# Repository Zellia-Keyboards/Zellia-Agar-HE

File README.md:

# Zellia-Agar-HE
## Use with Kicad 8.0.9
## Sensor just place SLSS49E for replace part in order later

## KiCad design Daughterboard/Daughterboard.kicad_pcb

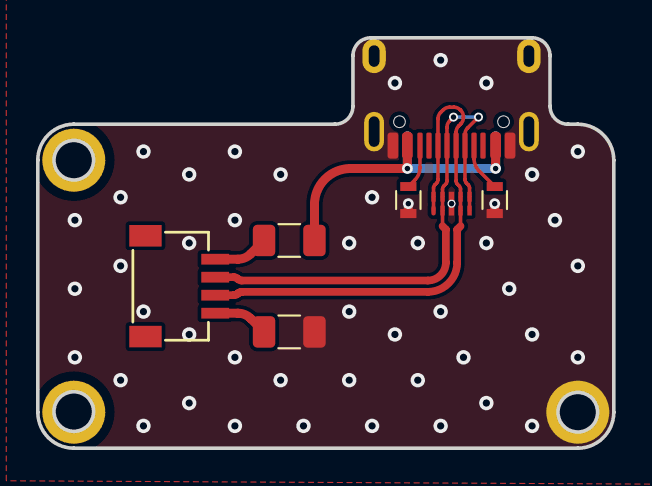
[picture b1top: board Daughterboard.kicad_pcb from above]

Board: 2 copper layers, 32.0 x 22.8 mm, 10 parts (0 on the bottom side), 8 nets.

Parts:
F1: ASMD1206-150; Fuse_1206_3216Metric
J1: TYPE-C-31-M12_13; TYPE-C-31-M-12
J4: SM04B-SRSS-TB(LF)(SN); JST-SR-4
L1: 60R@100MHz; L_1206_3216Metric
MH1, MH2, MH3: Mount-M2; Generic-Mounthole
R1, R2: 5.1k; R_0603
U1: TPD4E05U06DQAR; USON-10_2.5x1.0mm_P0.5mm

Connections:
CC1: J1.A5 (CC1), R1.1
CC2: J1.B5 (CC2), R2.1
DA+: J1.A6 (D+), J1.B6 (D+), J4.3, U1.1 (IO1), U1.4 (D2+), U1.7 (NC), U1.10 (NC)
DA-: J1.A7 (D-), J1.B7 (D-), J4.2, U1.2 (IO2), U1.5 (D2-), U1.6 (NC), U1.9 (NC)
GND: J4.4, L1.1
GNDPWR: J1.A1 (GND), J1.B1 (GND), J1.S (SHIELD), L1.2, MH2.1, R1.2, R2.2, U1.3 (GND), U1.8 (GND)
VBUS: F1.1, J1.A4 (VBUS), J1.B4 (VBUS)
VCC: F1.2, J4.1

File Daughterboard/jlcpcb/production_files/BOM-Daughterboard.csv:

Comment,Designator,Footprint,LCSC,Quantity
ASMD1206-150,F1,Fuse_1206_3216Metric,C135342,1
TPD4E05U06DQAR,U1,USON-10_2.5x1.0mm_P0.5mm,C138714,1
TYPE-C-31-M12_13,J1,TYPE-C-31-M-12,C165948,1
5.1k,"R1,R2",R_0603,C23186,2
SM04B-SRSS-TB(LF)(SN),J4,JST-SR-4,C2905006,1
60R@100MHz,L1,L_1206_3216Metric,C908349,1

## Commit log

2025-06-08 Add file via Upload
2025-06-08 add daughterboard
2025-06-30 Agar HE commit
2025-06-30 fixing stackup
2025-06-30 fixing production file
2025-07-05 Initial Push
2025-07-05 Revert "Initial Push"
2025-07-05 Production change
2025-07-06 Small Change
2025-07-06 Small fix
2025-07-06 Production fix
2025-07-18 add production for daughterboard
